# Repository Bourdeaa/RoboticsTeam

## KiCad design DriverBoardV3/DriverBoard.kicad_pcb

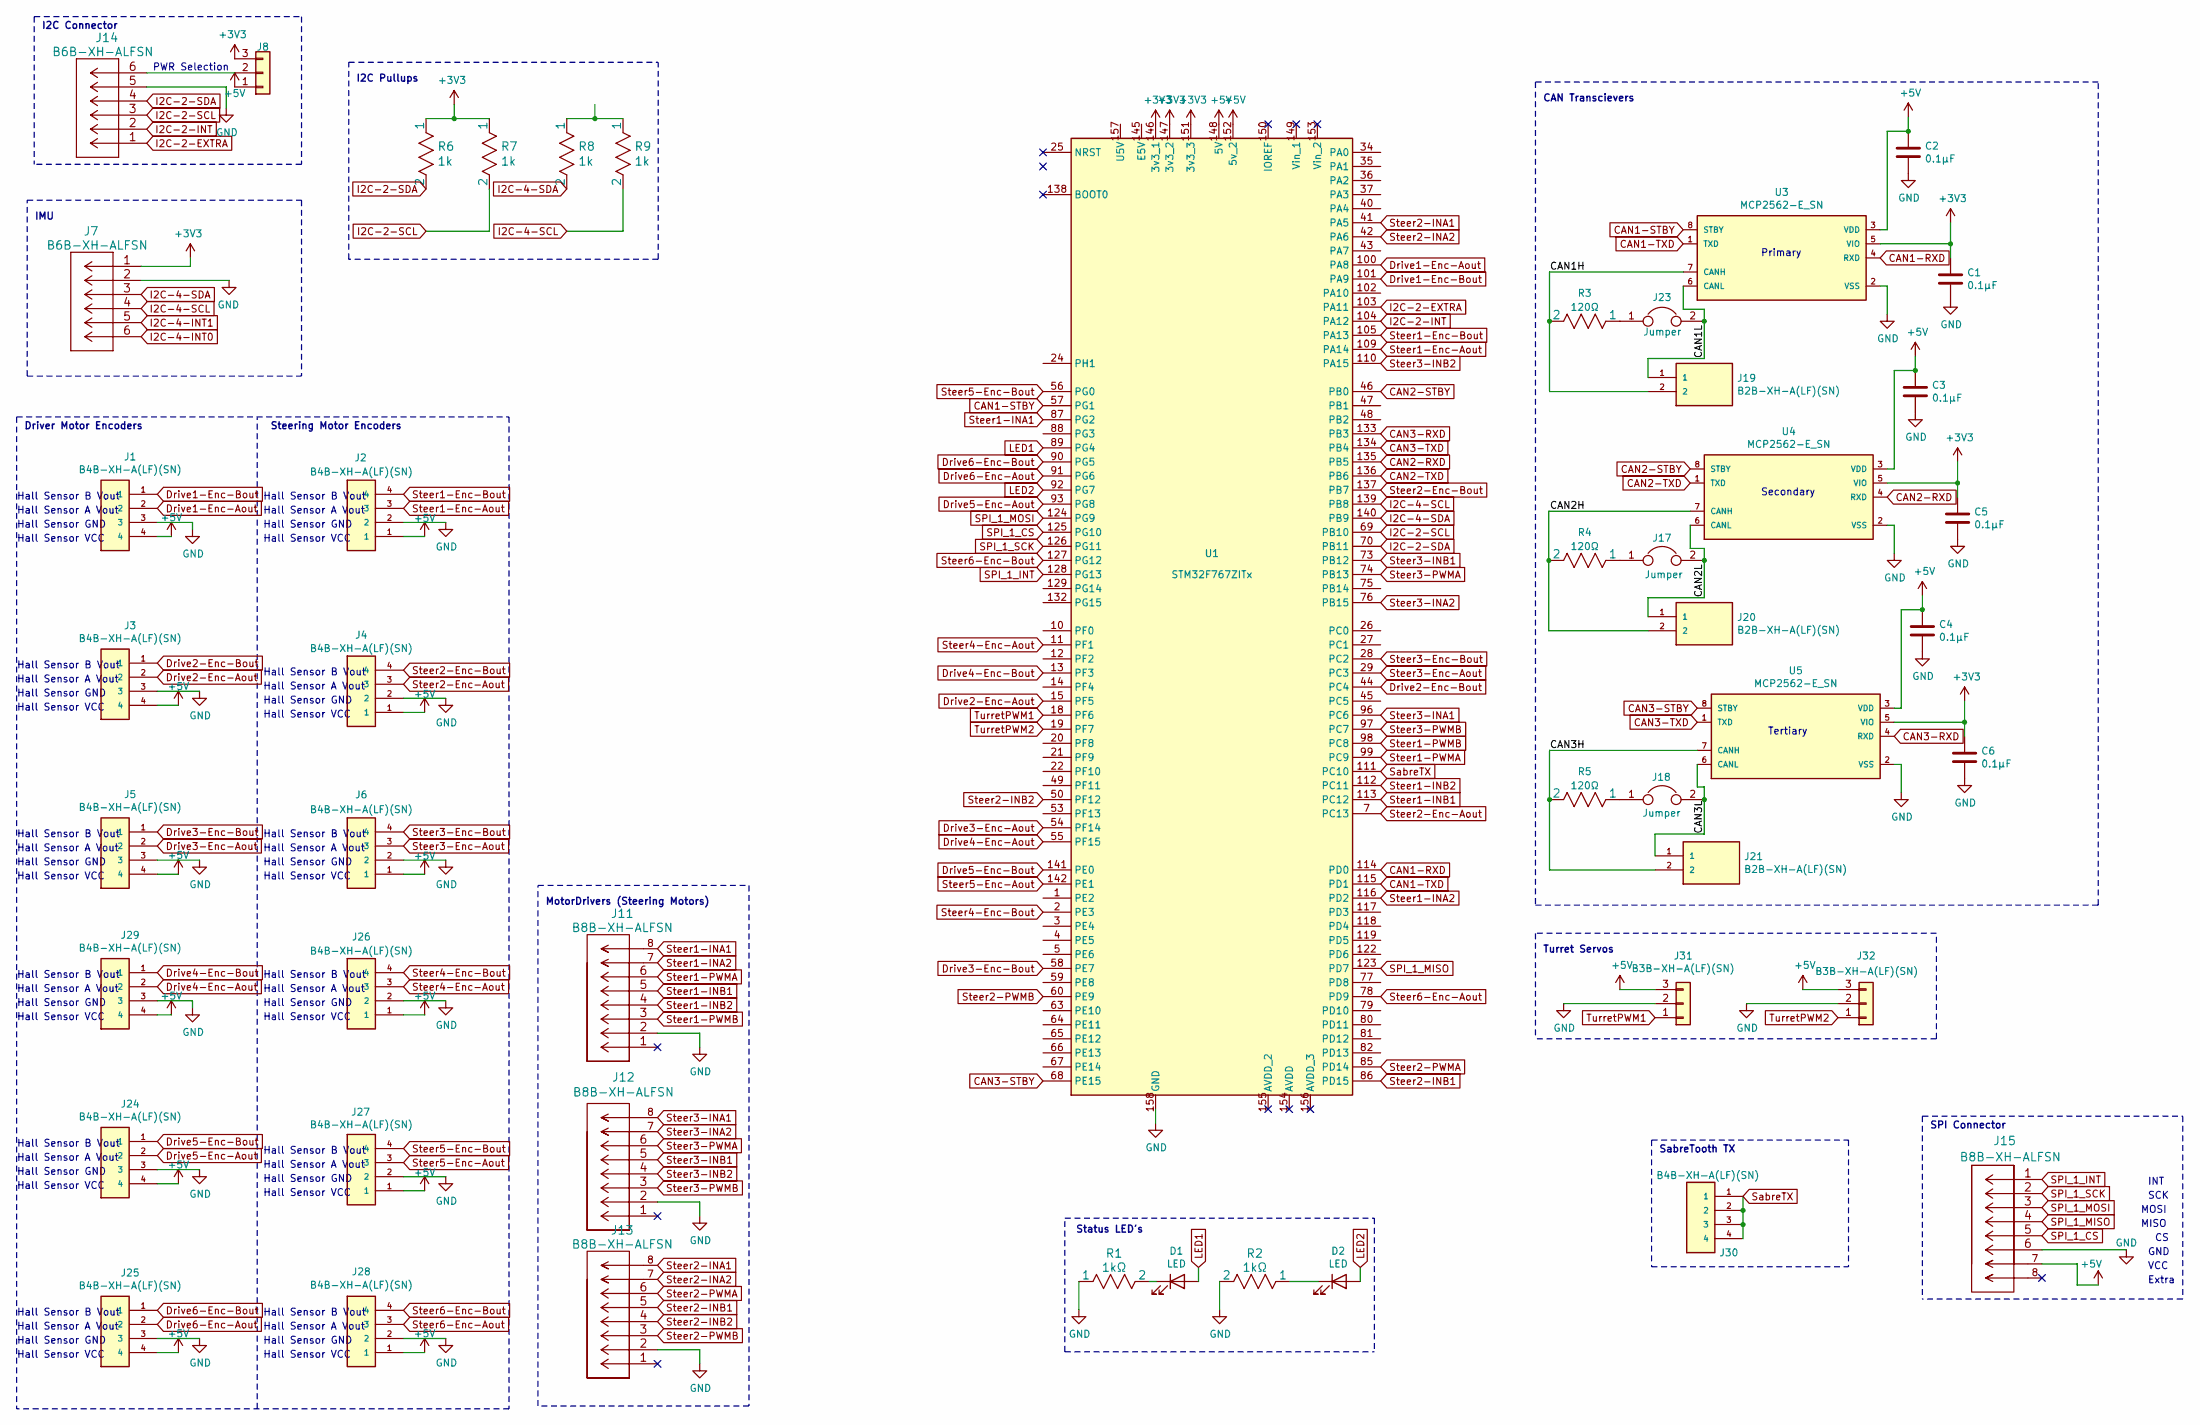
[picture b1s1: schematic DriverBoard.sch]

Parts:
C1: 0.1µF; Footprint_0603
C2, C3, C4, C5, C6: 0.1µF; C_0603_1608Metric_Pad1.08x0.95mm_HandSolder
D1, D2: LED; LY R976-PS-36
J1, J2, J3, J4, J5, J6, J24, J25, J26, J27, J28, J29, J30: B4B-XH-A(LF)(SN); JST4Way; PARTREV NA
J7, J14: B6B-XH-ALFSN; JST6Way
J8: Conn_01x03; PinHeader_1x03_P2.54mm_Vertical
J11, J12, J13, J15: B8B-XH-ALFSN; JST8Way
J17, J18, J23: Jumper; 2PinHeader
J19, J20, J21: B2B-XH-A(LF)(SN); JST2Way
J31, J32: B3B-XH-A(LF)(SN); JST3Way
R1, R2: 1kΩ; R_0603_1608Metric_Pad0.98x0.95mm_HandSolder
R3, R4, R5: 120Ω; R_0805_2012Metric_Pad1.20x1.40mm_HandSolder
R6, R7, R8, R9: 1k; R_0603_1608Metric_Pad0.98x0.95mm_HandSolder
U1: STM32F767ZITx; STM32
U3, U4, U5: MCP2562-E_SN; DIP787W45P254L1016H533Q8

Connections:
+3V3: C1.1, C5.1, C6.1, J7.1, J8.3, R6.1, R7.1, U1.146 (3v3_1), U1.147 (3v3_2), U1.151 (3v3_3), U3.5 (VIO), U4.5 (VIO), U5.5 (VIO)
+5V: C2.1, C3.1, C4.1, J1.4, J2.1, J3.4, J4.1, J5.4, J6.1, J8.1, J15.7, J24.4, J25.4, J26.1, J27.1, J28.1, J29.4, J31.3, J32.3, U1.148 (5V), U1.152 (5v_2), U3.3 (VDD), U4.3 (VDD), U5.3 (VDD); also elsewhere on the board
/CAN1H: J19.2, R3.2, U3.7 (CANH)
/CAN1L: J19.1, J23.2, U3.6 (CANL)
/CAN2H: J20.2, R4.2, U4.7 (CANH)
/CAN2L: J17.2, J20.1, U4.6 (CANL)
/CAN3H: J21.2, R5.2, U5.7 (CANH)
/CAN3L: J18.2, J21.1, U5.6 (CANL)
CAN1-RXD: U1.114 (PD0), U3.4 (RXD)
CAN1-STBY: U1.57 (PG1), U3.8 (STBY)
CAN1-TXD: U1.115 (PD1), U3.1 (TXD)
CAN2-RXD: U1.135 (PB5), U4.4 (RXD)
CAN2-STBY: U1.46 (PB0), U4.8 (STBY)
CAN2-TXD: U1.136 (PB6), U4.1 (TXD)
CAN3-RXD: U1.133 (PB3), U5.4 (RXD)
CAN3-STBY: U1.68 (PE15), U5.8 (STBY)
CAN3-TXD: U1.134 (PB4), U5.1 (TXD)
Drive1-Enc-Aout: J1.2, U1.100 (PA8)
Drive1-Enc-Bout: J1.1, U1.101 (PA9)
Drive2-Enc-Aout: J3.2, U1.15 (PF5)
Drive2-Enc-Bout: J3.1, U1.44 (PC4)
Drive3-Enc-Aout: J5.2, U1.54 (PF14)
Drive3-Enc-Bout: J5.1, U1.58 (PE7)
Drive4-Enc-Aout: J29.2, U1.55 (PF15)
Drive4-Enc-Bout: J29.1, U1.13 (PF3)
Drive5-Enc-Aout: J24.2, U1.93 (PG8)
Drive5-Enc-Bout: J24.1, U1.141 (PE0)
Drive6-Enc-Aout: J25.2, U1.91 (PG6)
Drive6-Enc-Bout: J25.1, U1.90 (PG5)
GND: C1.2, C2.2, C3.2, C4.2, C5.2, C6.2, J1.3, J2.2, J3.3, J4.2, J5.3, J6.2, J7.2, J11.2, J12.2, J13.2, J14.5, J15.6, J24.3, J25.3, J26.2, J27.2, J28.2, J29.3, J31.2, J32.2, R1.1, R2.2, U1.158 (GND), U3.2 (VSS), U4.2 (VSS), U5.2 (VSS); also elsewhere on the board
I2C-2-EXTRA: J14.1, U1.103 (PA11)
I2C-2-INT: J14.2, U1.104 (PA12)
I2C-2-SCL: J14.3, R7.2, U1.69 (PB10)
I2C-2-SDA: J14.4, R6.2, U1.70 (PB11)
I2C-4-INT0: J7.6
I2C-4-INT1: J7.5
I2C-4-SCL: J7.4, R9.2, U1.139 (PB8)
I2C-4-SDA: J7.3, R8.2, U1.140 (PB9)
LED1: D1.2 (A), U1.89 (PG4)
LED2: D2.2 (A), U1.92 (PG7)
unnamed: D1.1 (K), R1.2
unnamed: D2.1 (K), R2.1
unnamed: J8.2, J14.6
unnamed: J17.1, R4.1
unnamed: J18.1, R5.1
unnamed: J23.1, R3.1
unnamed: R8.1, R9.1
SPI_1_CS: J15.5, U1.125 (PG10)
SPI_1_INT: J15.1, U1.128 (PG13)
SPI_1_MISO: J15.4, U1.123 (PD7)
SPI_1_MOSI: J15.3, U1.124 (PG9)
SPI_1_SCK: J15.2, U1.126 (PG11)
SabreTX: J30.1, J30.2, J30.3, J30.4, U1.111 (PC10)
Steer1-Enc-Aout: J2.3, U1.109 (PA14)
Steer1-Enc-Bout: J2.4, U1.105 (PA13)
Steer1-INA1: J11.8, U1.87 (PG2)
Steer1-INA2: J11.7, U1.116 (PD2)
Steer1-INB1: J11.5, U1.113 (PC12)
Steer1-INB2: J11.4, U1.112 (PC11)
Steer1-PWMA: J11.6, U1.99 (PC9)
Steer1-PWMB: J11.3, U1.98 (PC8)
Steer2-Enc-Aout: J4.3, U1.7 (PC13)
Steer2-Enc-Bout: J4.4, U1.137 (PB7)
Steer2-INA1: J13.8, U1.41 (PA5)
Steer2-INA2: J13.7, U1.42 (PA6)
Steer2-INB1: J13.5, U1.86 (PD15)
Steer2-INB2: J13.4, U1.50 (PF12)
Steer2-PWMA: J13.6, U1.85 (PD14)
Steer2-PWMB: J13.3, U1.60 (PE9)
Steer3-Enc-Aout: J6.3, U1.29 (PC3)
Steer3-Enc-Bout: J6.4, U1.28 (PC2)
Steer3-INA1: J12.8, U1.96 (PC6)
Steer3-INA2: J12.7, U1.76 (PB15)
Steer3-INB1: J12.5, U1.73 (PB12)
Steer3-INB2: J12.4, U1.110 (PA15)
Steer3-PWMA: J12.6, U1.74 (PB13)
Steer3-PWMB: J12.3, U1.97 (PC7)
Steer4-Enc-Aout: J26.3, U1.11 (PF1)
Steer4-Enc-Bout: J26.4, U1.2 (PE3)
Steer5-Enc-Aout: J27.3, U1.142 (PE1)
Steer5-Enc-Bout: J27.4, U1.56 (PG0)
Steer6-Enc-Aout: J28.3, U1.78 (PD9)
Steer6-Enc-Bout: J28.4, U1.127 (PG12)
TurretPWM1: J31.1, U1.18 (PF6)
TurretPWM2: J32.1, U1.19 (PF7)

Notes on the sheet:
Driver Motor Encoders
Hall Sensor B Vout
Hall Sensor A Vout
Hall Sensor GND
Hall Sensor VCC
I2C Connector
SPI Connector
MOSI
GND
VCC
MISO
Status LED's
IMU
MotorDrivers (Steering Motors)
SCK
INT
Extra
CAN Transcievers
Primary
Secondary
Tertiary
SabreTooth TX
Steering Motor Encoders
Turret Servos
I2C Pullups
PWR Selection

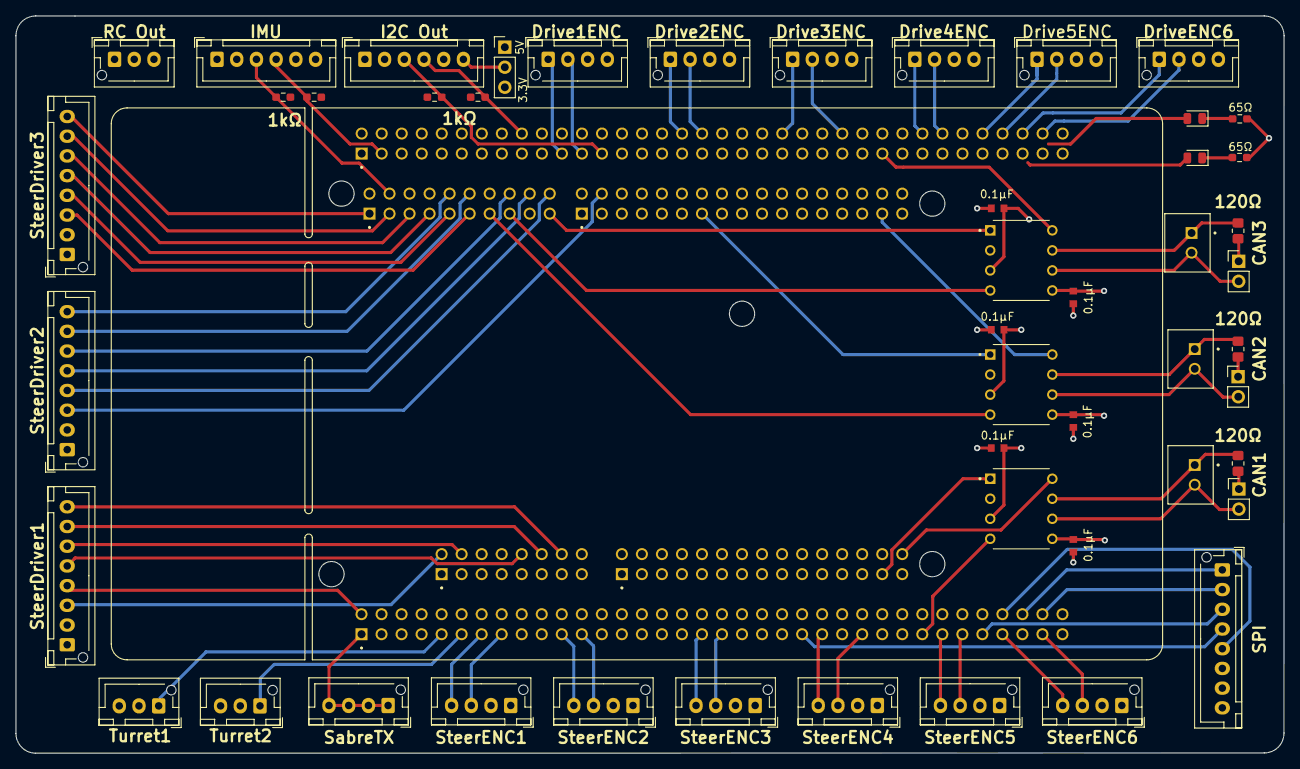
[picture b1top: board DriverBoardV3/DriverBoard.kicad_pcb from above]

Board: 4 copper layers, 160.8 x 93.5 mm, 50 parts (0 on the bottom side), 83 nets.

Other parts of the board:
Ce: 0.1µF; Footprint_0603
J8#2: B3B-XH-A(LF)(SN); JST3Way

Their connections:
+5V: Ce.1; also elsewhere on the board
GND: Ce.2; also elsewhere on the board

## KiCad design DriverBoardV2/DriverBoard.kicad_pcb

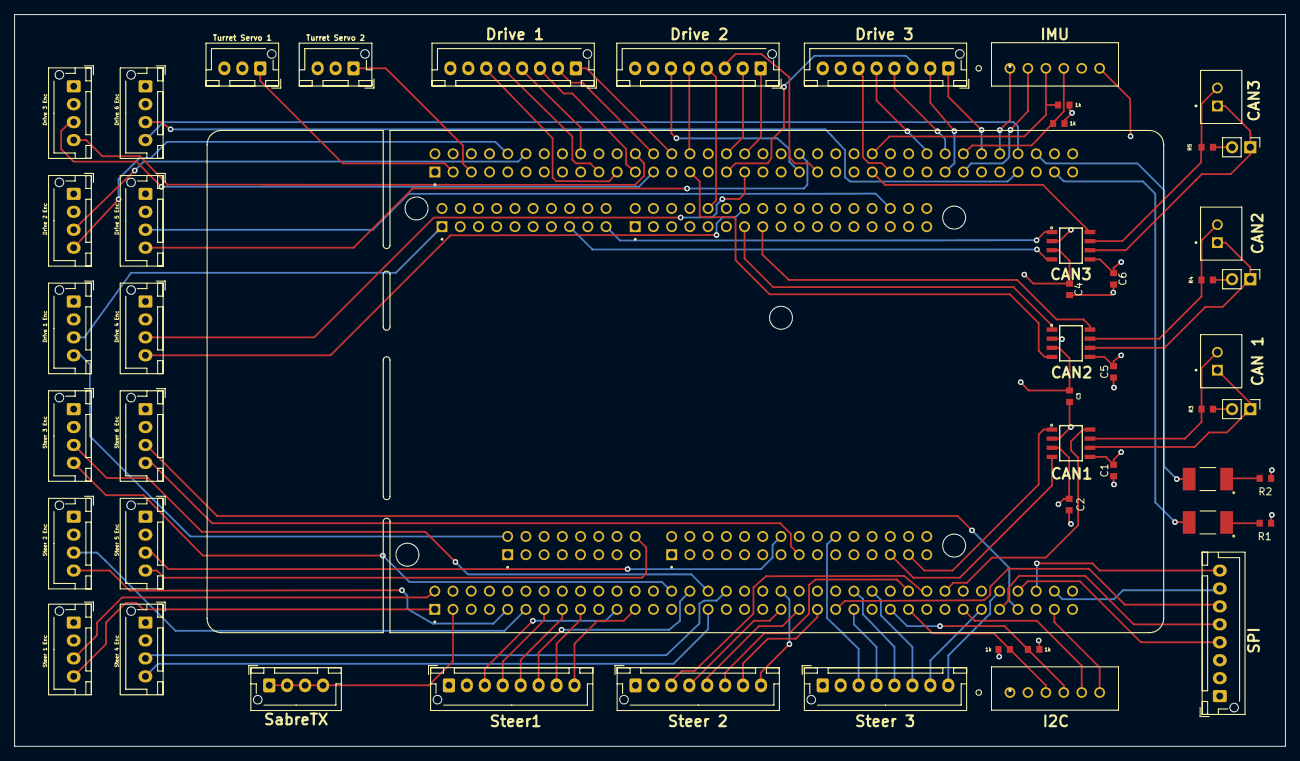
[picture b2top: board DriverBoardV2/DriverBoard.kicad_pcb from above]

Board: 4 copper layers, 177.2 x 102.0 mm, 51 parts (0 on the bottom side), 98 nets.

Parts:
C1, C2, C3, C4, C5, C6: 0.1µF; 0603Footprint
D1, D2: LED; 1812Footprint
J1, J2, J3, J4, J5, J6, J24, J25, J26, J27, J28, J29, J30: B4B-XH-A(LF)(SN); JST4Way
J7, J14: B6B-XH-ALFSN; JST6Way
J8, J9, J10, J11, J12, J13, J15: B8B-XH-ALFSN; JST8Way
J17, J18, J23: Jumper; 2PinHeader
J19, J20, J21: B2B-XH-A(LF)(SN); JST2Way
J31, J32: B3B-XH-A(LF)(SN); JST3Way
R1, R2: 1kΩ; 0603Footprint
R3, R4, R5: 120Ω; 0603Footprint
R6, R7, R8, R9: 1k; Footprint_0603
U1: STM32F767ZITx; STM32
U3, U4, U5: MCP2562-E_SN; MCP2562

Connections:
+3V3: C1.1, C5.1, C6.1, J7.1, U1.146, U1.147, U1.151, U3.5, U4.5, U5.5
+5V: C2.1, C3.1, C4.1, J1.4, J2.4, J3.4, J4.4, J5.4, J6.4, J14.6, J15.2, J24.4, J25.4, J26.4, J27.4, J28.4, J29.4, J31.1, J32.1, R6.1, R7.1, R8.1, R9.1, U1.148, U1.152, U3.3, U4.3, U5.3
CAN1-RXD: U1.114, U3.4
CAN1-STBY: U1.57, U3.8
CAN1-TXD: U1.115, U3.1
CAN2-RXD: U1.135, U4.4
CAN2-STBY: U1.48, U4.8
CAN2-TXD: U1.136, U4.1
CAN3-RXD: U1.133, U5.4
CAN3-STBY: U1.65, U5.8
CAN3-TXD: U1.134, U5.1
Drive1-Enc-Aout: J1.2, U1.96
Drive1-Enc-Bout: J1.1, U1.98
Drive1-INA1: J8.8, U1.75
Drive1-INA2: J8.7, U1.76
Drive1-INB1: J8.5, U1.70
Drive1-INB2: J8.4, U1.97
Drive1-PWMA: J8.6, U1.100
Drive1-PWMB: J8.3, U1.101
Drive2-B1: J9.5, U1.66
Drive2-B2: J9.4, U1.74
Drive2-Enc-Aout: J3.2, U1.104
Drive2-Enc-Bout: J3.1, U1.77
Drive2-INA1: J9.8, U1.15
Drive2-INA2: J9.7, U1.44
Drive2-PWMA: J9.6, U1.81
Drive2-PWMB: J9.3, U1.82
Drive3-Enc-Aout: J5.2, U1.69
Drive3-Enc-Bout: J5.1, U1.47
Drive3-INA1: J10.8, U1.49
Drive3-INA2: J10.7, U1.53
Drive3-INB1: J10.5, U1.13
Drive3-INB2: J10.4, U1.64
Drive3-PWMA: J10.6, U1.102
Drive3-PWMB: J10.3, U1.67
Drive4-Enc-Aout: J29.2, U1.36
Drive4-Enc-Bout: J29.1, U1.129
Drive5-Enc-Aout: J24.2, U1.68
Drive5-Enc-Bout: J24.1, U1.22
Drive6-Enc-Aout: J25.2, U1.79
Drive6-Enc-Bout: J25.1, U1.93
GND: C1.2, C2.2, C3.2, C4.2, C5.2, C6.2, J1.3, J2.3, J3.3, J4.3, J5.3, J6.3, J7.2, J8.2, J9.2, J10.2, J11.2, J12.2, J13.2, J14.5, J15.3, J24.3, J25.3, J26.3, J27.3, J28.3, J29.3, J31.2, J32.2, R1.1, R2.2, U1.158, U3.2, U4.2, U5.2
I2C-2-EXTRA: J14.1, U1.12, U1.78
I2C-2-INT: J14.2, U1.56
I2C-2-SCL: J14.3, R7.2, U1.11
I2C-2-SDA: J14.4, R6.2, U1.10
I2C-4-INT0: J7.6, U1.141
I2C-4-INT1: J7.5, U1.50
I2C-4-SCL: J7.4, R9.2, U1.54
I2C-4-SDA: J7.3, R8.2, U1.55
LED1: D1.2, U1.89
LED2: D2.2, U1.90
unnamed: D1.1, R1.2
unnamed: D2.1, R2.1
unnamed: J17.1, J17.2, J20.1, R4.1, U4.6
unnamed: J18.1, J18.2, J21.1, R5.1, U5.6
unnamed: J19.1, J23.1, J23.2, R3.1, U3.6
unnamed: J19.2, R3.2, U3.7
unnamed: J20.2, R4.2, U4.7
unnamed: J21.2, R5.2, U5.7
SPI_1_CS: J15.4, U1.125
SPI_1_INT: J15.8, U1.128
SPI_1_MISO: J15.5, U1.124
SPI_1_MOSI: J15.6, U1.123
SPI_1_SCK: J15.7, U1.126
SabreTX: J30.1, J30.2, J30.3, J30.4, U1.113
Steer1-Enc-Aout: J2.2, U1.112
Steer1-Enc-Bout: J2.1, U1.111
Steer1-INA1: J11.8, U1.7
Steer1-INA2: J11.7, U1.110
Steer1-INB1: J11.5, U1.109
Steer1-INB2: J11.4, U1.105
Steer1-PWMA: J11.6, U1.41
Steer1-PWMB: J11.3, U1.137
Steer2-Enc-Aout: J4.2, U1.19
Steer2-Enc-Bout: J4.1, U1.18
Steer2-INA1: J12.8, U1.117
Steer2-INA2: J12.7, U1.122
Steer2-INB1: J12.5, U1.119
Steer2-INB2: J12.4, U1.118
Steer2-PWMA: J12.6, U1.20
Steer2-PWMB: J12.3, U1.21
Steer3-Enc-Aout: J6.2, U1.40
Steer3-Enc-Bout: J6.1, U1.34
Steer3-INA1: J13.8, U1.132
Steer3-INA2: J13.7, U1.142
Steer3-INB1: J13.5, U1.3
Steer3-INB2: J13.4, U1.2
Steer3-PWMA: J13.6, U1.4, U1.85
Steer3-PWMB: J13.3, U1.5, U1.86
Steer4-Enc-Aout: J26.2, U1.46
Steer4-Enc-Bout: J26.1, U1.24
Steer5-Enc-Aout: J27.2, U1.1
Steer5-Enc-Bout: J27.1, U1.88
Steer6-Enc-Aout: J28.2, U1.127
Steer6-Enc-Bout: J28.1, U1.43
TurretPWM1: J31.3, U1.139
TurretPWM2: J32.3, U1.140

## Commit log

2022-01-05 Add files via upload
    Connected 4 of the 6 drivers and cleaned up some of the placement connections
2022-01-07 Add files via upload
    Layed out the remainder of the connectors and changed some of the schematic stuff
2022-02-07 Add files via upload
    FinalDesign For DriverBoard (Feb6th 2022)
2022-04-09 Update MCP2562 Data Sheet.pdf, TB67H420FTG_datasheet_en_20170818.pdf, and 47 more files...
2022-04-11 Update DriverBoard-rescue.dcm, DriverBoard-rescue.lib, and 33 more files...
2022-04-18 Update CoopReport.docx, DriverBoard-cache.lib, and 18 more files...
2022-04-23 Update DriverBoard.kicad_pcb and DriverBoard.kicad_pcb-bak
2022-04-24 Update DriverBoard.kicad_pcb, DriverBoard.kicad_pcb-bak, and 39 more files...

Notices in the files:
parts and their libraries:
Copyright 2021 Accelerated Designs. All rights reserved.
